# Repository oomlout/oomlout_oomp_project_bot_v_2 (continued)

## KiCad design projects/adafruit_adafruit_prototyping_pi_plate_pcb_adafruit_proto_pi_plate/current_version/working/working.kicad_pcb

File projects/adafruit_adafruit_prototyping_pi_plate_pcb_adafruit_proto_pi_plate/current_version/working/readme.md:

# adafruit_prototyping_pi_plate_pcb
 
## summary 
* id: adafruit_adafruit_prototyping_pi_plate_pcb_adafruit_proto_pi_plate
* user: adafruit
* name: adafruit_prototyping_pi_plate_pcb
* board: adafruit_proto_pi_plate
* repo: https://github.com/adafruit/Adafruit-Prototyping-Pi-Plate-PCB

* src_file_repo_sch: 
* src_file_repo_sch_link: https://github.com/adafruit/Adafruit-Prototyping-Pi-Plate-PCB/tree/master/
* full details link: https://github.com/oomlout/oomlout_oomp_project_bot_v_2/tree/main/projects/adafruit_adafruit_prototyping_pi_plate_pcb_adafruit_proto_pi_plate/current_version/working  

## schematic  
  
[schematic (pdf)](working_schematic.pdf) 

## pcb  

[board (pdf)](working.pdf)  

## working_bom
| Id | Designator | Footprint | Quantity | Designation | Supplier and ref |  | None | 
| --- | --- | --- | --- | --- | --- | --- | --- | 
| 1 | J3 | 1X05-3.5MM | 1 | 1X5 |  |  | [''] | 
| 2 | CN1,CN3,CN2 | 1X04-3.5MM | 3 | 1X4-3.5MM |  |  | [''] | 
| 3 | JP4,JP2,JP6,JP5 | 1X08-BIG | 4 |  |  |  | [''] | 
| 4 | JP3 | 1X06-BIG | 1 |  |  |  | [''] | 
| 5 | U$1 | RASBERRYPI_SHIELD | 1 | RASPBERRYPI_BB |  |  | [''] | 
| 6 | CN4 | 1X04-CLEANBIG | 1 | 1X4-CLEANBIG |  |  | [''] | 
| 7 | JP1 | 1X08-3.5MM | 1 |  |  |  | [''] | 
| 8 | U$3 | ADAFRUIT_TEXT_20MM | 1 |  |  |  | [''] | 
| 9 | U$2 | SO-16NMW | 1 | SMD-16SOIC |  |  | [''] | 
| 10 | J1,J2 | 1X2-3.5MM | 2 | 1X2-3.5MM |  |  | [''] | 

## bom_schematic
| Ref | Qnty | Value | Cmp name | Footprint | Description | Vendor | DNP | 
| --- | --- | --- | --- | --- | --- | --- | --- | 
| CN1, CN2, CN3 | 3 | 1X4-3.5MM | 1X4-3.5MM | working:1X04-3.5MM |  |  |  | 
| CN4 | 1 | 1X4-CLEANBIG | 1X4-CLEANBIG | working:1X04-CLEANBIG |  |  |  | 
| J1, J2 | 2 | 1X2-3.5MM | 1X2-3.5MM | working:1X2-3.5MM |  |  |  | 
| J3 | 1 | 1X5 | 1X5 | working:1X05-3.5MM |  |  |  | 
| JP1 | 1 | PINHD-1X8-3.5MM | PINHD-1X8-3.5MM | working:1X08-3.5MM |  |  |  | 
| JP2, JP4, JP5, JP6 | 4 | PINHD-1X8BIG | PINHD-1X8BIG | working:1X08-BIG |  |  |  | 
| JP3 | 1 | PINHD-1X6B | PINHD-1X6B | working:1X06-BIG |  |  |  | 
| U$1 | 1 | RASPBERRYPI_BB | RASPBERRYPI_BB | working:RASBERRYPI_SHIELD |  |  |  | 
| U$2 | 1 | SMD-16SOIC | SMD-16SOIC | working:SO-16NMW |  |  |  |

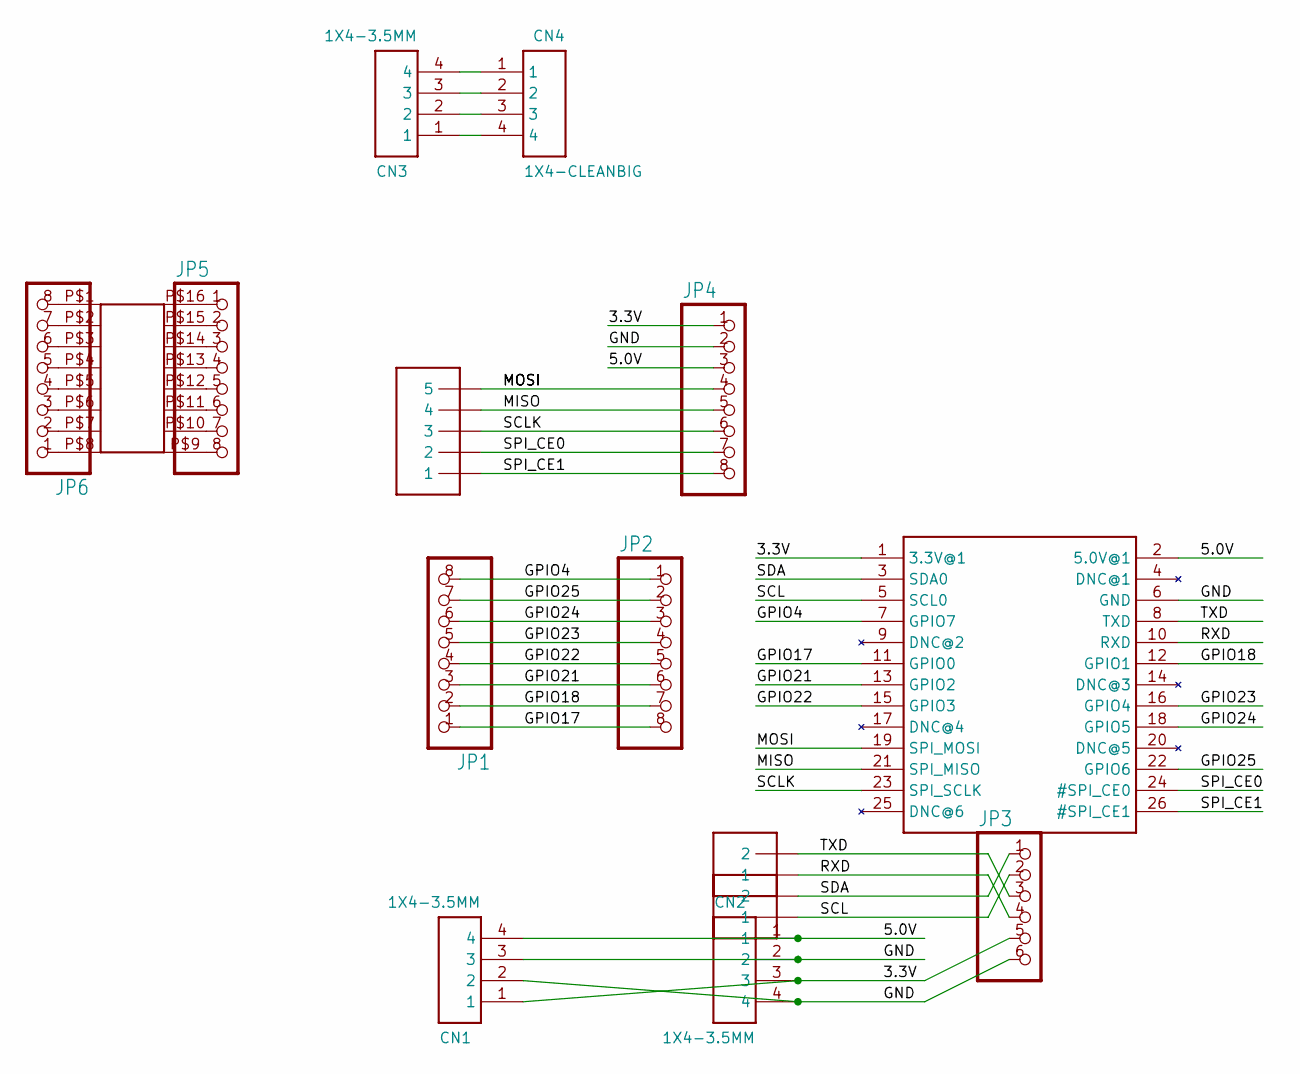
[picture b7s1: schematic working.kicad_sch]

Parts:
CN1, CN2, CN3: 1X4-3.5MM; 1X04-3.5MM
CN4: 1X4-CLEANBIG; 1X04-CLEANBIG
J1, J2: 1X2-3.5MM
J3: 1X5; 1X05-3.5MM
JP1: PINHD-1X8-3.5MM; 1X08-3.5MM
JP2, JP4, JP5, JP6: PINHD-1X8BIG; 1X08-BIG
JP3: PINHD-1X6B; 1X06-BIG
U$1: RASPBERRYPI_BB; RASBERRYPI_SHIELD
U$2: SMD-16SOIC; SO-16NMW

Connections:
3.3V: CN1.1, CN2.3, JP3.5, JP4.1, U$1.1 (3.3V@1)
5.0V: CN1.4, CN2.1, JP4.3, U$1.2 (5.0V@1)
GND: CN1.2, CN1.3, CN2.2, CN2.4, JP3.6, JP4.2, U$1.6 (GND)
GPIO4: JP1.8, JP2.1, U$1.7 (GPIO7)
GPIO17: JP1.1, JP2.8, U$1.11 (GPIO0)
GPIO18: JP1.2, JP2.7, U$1.12 (GPIO1)
GPIO21: JP1.3, JP2.6, U$1.13 (GPIO2)
GPIO22: JP1.4, JP2.5, U$1.15 (GPIO3)
GPIO23: JP1.5, JP2.4, U$1.16 (GPIO4)
GPIO24: JP1.6, JP2.3, U$1.18 (GPIO5)
GPIO25: JP1.7, JP2.2, U$1.22 (GPIO6)
MISO: J3.4, JP4.5, U$1.21 (SPI_MISO)
MOSI: J3.5, JP4.4, U$1.19 (SPI_MOSI)
unnamed: JP5.1, U$2.P$16
unnamed: JP5.2, U$2.P$15
unnamed: JP5.3, U$2.P$14
unnamed: JP5.4, U$2.P$13
unnamed: JP5.5, U$2.P$12
unnamed: JP5.6, U$2.P$11
unnamed: JP5.7, U$2.P$10
unnamed: JP5.8, U$2.P$9
unnamed: JP6.1, U$2.P$8
unnamed: JP6.2, U$2.P$7
unnamed: JP6.3, U$2.P$6
unnamed: JP6.4, U$2.P$5
unnamed: JP6.5, U$2.P$4
unnamed: JP6.6, U$2.P$3
unnamed: JP6.7, U$2.P$2
unnamed: JP6.8, U$2.P$1
unnamed: CN3.4, CN4.1
unnamed: CN3.3, CN4.2
unnamed: CN3.2, CN4.3
unnamed: CN3.1, CN4.4
RXD: J2.1, JP3.4, U$1.10 (RXD)
SCL: J1.1, JP3.2, U$1.5 (SCL0)
SCLK: J3.3, JP4.6, U$1.23 (SPI_SCLK)
SDA: J1.2, JP3.1, U$1.3 (SDA0)
SPI_CE0: J3.2, JP4.7, U$1.24 (#SPI_CE0)
SPI_CE1: J3.1, JP4.8, U$1.26 (#SPI_CE1)
TXD: J2.2, JP3.3, U$1.8 (TXD)

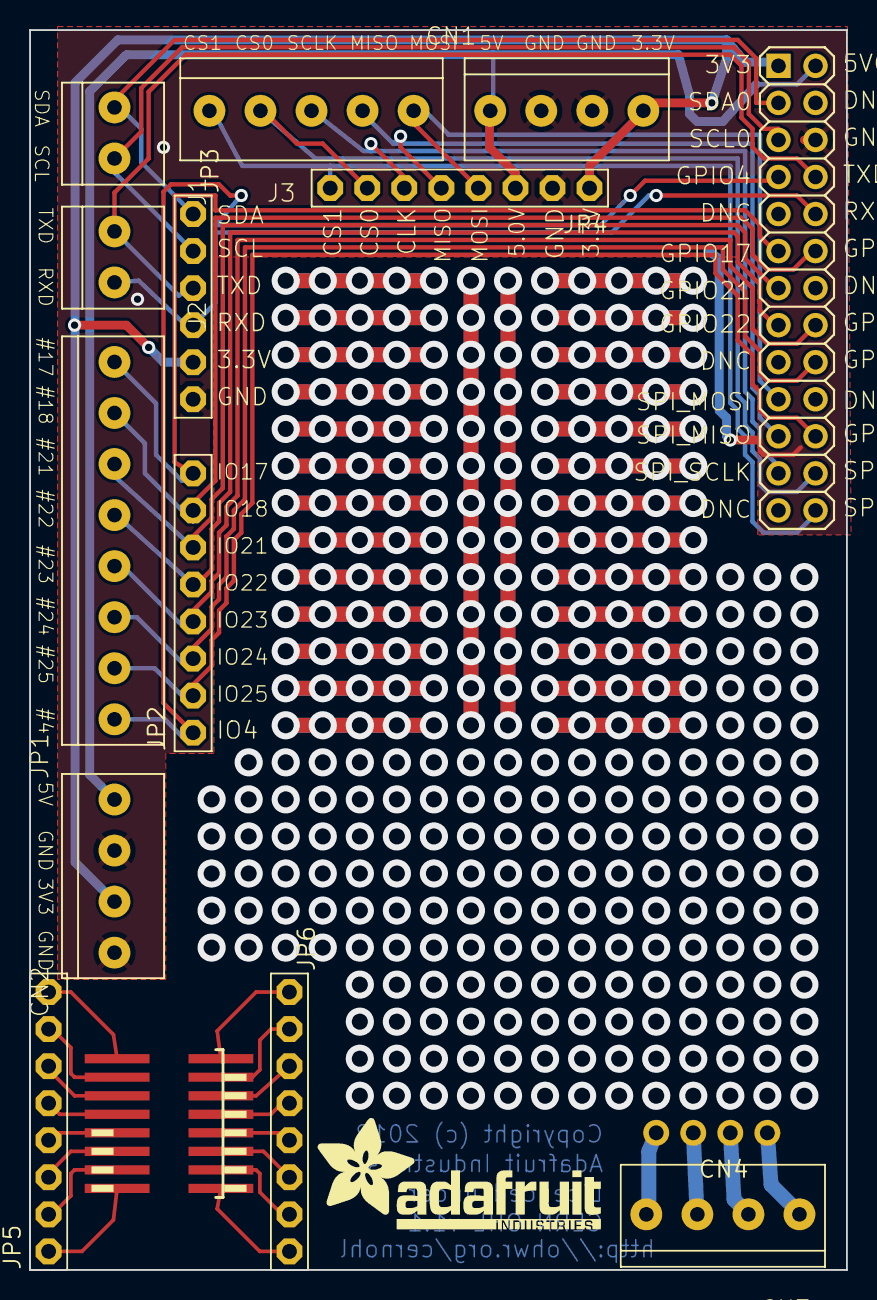
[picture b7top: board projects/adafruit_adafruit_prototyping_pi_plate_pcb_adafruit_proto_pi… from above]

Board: 16 copper layers, 56.0 x 85.0 mm, 16 parts (0 on the bottom side), 40 nets.

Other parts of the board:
U$3: ADAFRUIT_TEXT_20MM
